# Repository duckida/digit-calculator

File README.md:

# my digit calculator

This is a calculator for the [Hack Club Digit](https://digit.smol.hackclub.com/) YSWS!

## Features
- Controlled by a XIAO ESP32-C3 
- BlackBerry-style trackball with RGB LED
- I2C OLED to display menus and calculations
- Support for LiPo battery and switch

## bill of materials
| Item                 | Quantity | Merchant     | Price (USD) |
|----------------------|----------|--------------|-------------|
| XIAO ESP32-C3        | 1        | Seeed Studio | $4.90       |
| BlackBerry Trackball | 1        | AliExpress   | $1.34       |
| SSD1306 OLED         | 1        | AliExpress   | $1.34       |
| PCB                  | 1        | JLCPCB       | ~           |
| Switch               | 1        | AliExpress   | Free        |
| LiPo battery         | 1        | AliExpress   | $1.34       |

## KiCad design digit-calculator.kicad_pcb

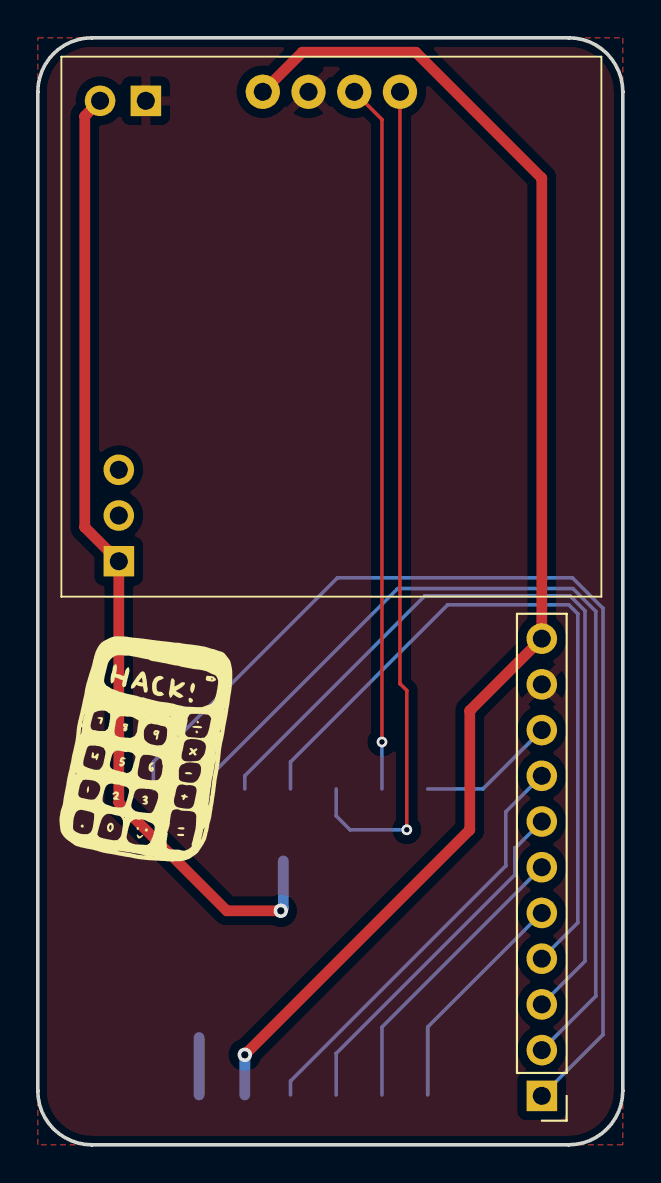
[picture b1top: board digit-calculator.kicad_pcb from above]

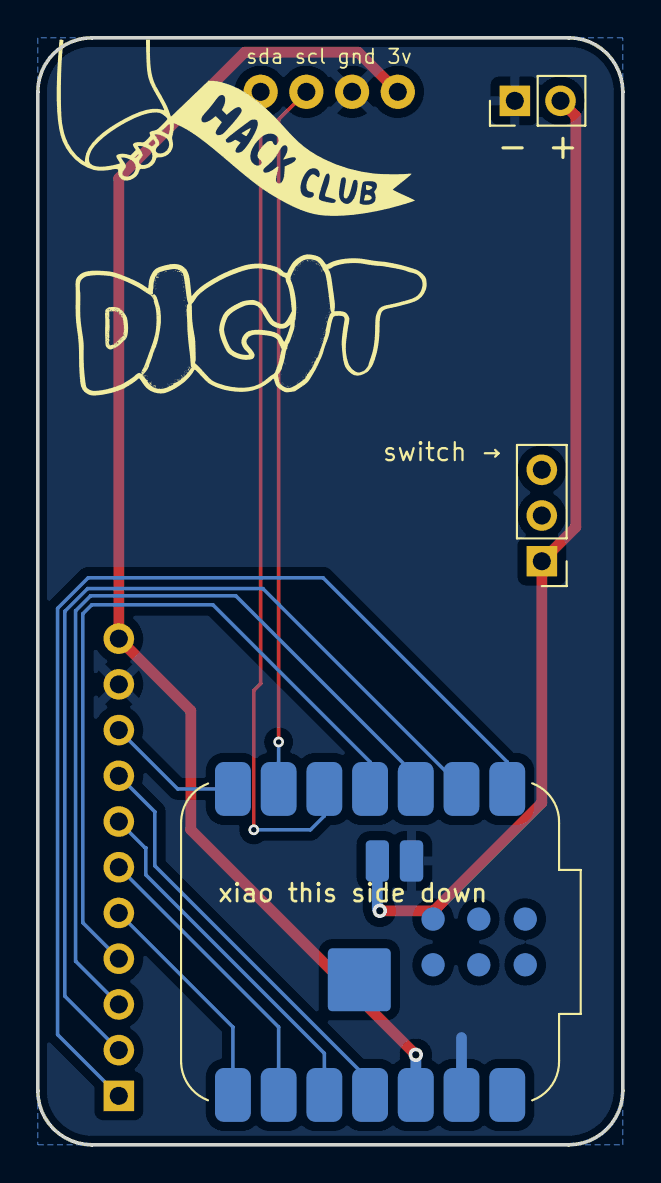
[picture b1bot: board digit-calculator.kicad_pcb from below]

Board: 2 copper layers, 32.5 x 61.5 mm, 6 parts (4 on the bottom side), 14 nets.

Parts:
Brd1: SSD1306; SSD1306-OLED
J1: Trackball; PinHeader_1x11_P2.54mm_Vertical
J2: - +; PinHeader_1x02_P2.54mm_Vertical
SW1: Switch; PinHeader_1x03_P2.54mm_Vertical
U1: xiao this side down; MCU_Seeed_ESP32C3
logo: LOGO

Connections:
+3V3: Brd1.1 (GND), J1.11 (VCC), U1.12 (3V3)
+BATT: J2.2, SW1.1 (A), U1.16
/BTN: J1.9 (BTN), U1.7 (GPIO21_D6_TX)
/J_DOWN: J1.6 (DWN), U1.9 (GPIO8_D8_SCK)
/J_LEFT: J1.7 (LFT), U1.10 (GPIO9_D9_MISO)
/J_RIGHT: J1.8 (RHT), U1.11 (GPIO10_D10_MOSI)
/J_UP: J1.5 (UP), U1.8 (GPIO20_D7_RX)
/LED_B: J1.1 (BLU), U1.1 (GPIO2_A0_D0)
/LED_G: J1.3 (GRN), U1.3 (GPIO4_A2_D2)
/LED_R: J1.2 (RED), U1.2 (GPIO3_A1_D1)
/LED_W: J1.4 (WHT), U1.4 (GPIO5_A3_D3)
/SCL: Brd1.2 (VCC), U1.6 (GPIO7_D5_SCL)
/SDA: Brd1.4 (SDA), U1.5 (GPIO6_D4_SDA)
GND: Brd1.2 (VCC), J1.10 (GND), J2.1, U1.13 (GND), U1.17

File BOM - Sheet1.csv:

Item,Quantity,Link,Price (USD)
XIAO ESP32-C3,1,Seeed Studio,$4.90
BlackBerry Trackball,1,AliExpress,$1.34
SSD1306 OLED,1,AliExpress,$1.34
PCB,1,JLCPCB,~
